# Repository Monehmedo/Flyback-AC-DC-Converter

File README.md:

Flyback AC-DC Converter — 12V SMPS
PCB Design Project | KiCad 10.0.1 | Mohamed Elashmawi
A complete Switch-Mode Power Supply (SMPS) designed from scratch using the Flyback
topology, converting 230VAC mains input to a regulated 12V DC output. This project
covers full schematic design, PCB layout, and 3D validation.

⚡Specifications

Parameter Value

Input Voltage 230VAC (50Hz)
Output Voltage 12V DC

Topology Flyback (Isolated SMPS)

PWM Controller VIPer22A (DIP-8)

Transformer EE25-13-7

Rectifier Bridge KBP206

Output Diode SB360 (Schottky)

Feedback / Isolation EL817 Optocoupler + TL431

Input Protection Varistor + NTC Thermistor + Fuse (500mA)

EMI Filter Schaffner RN102-0.3-02-12M

🔧Circuit Architecture

The design is divided into four functional blocks:

1.🔌Input Filter ( Eingangsfilter )

Varistor (RV1): Overvoltage/surge protection

NTC Thermistor (TH1): Inrush current limiting at startup

EMI Filter (FL1 - Schaffner RN102): Common-mode noise suppression

Fuse (F1 - 500mA): Short-circuit protection

X-Capacitor (C1 - 100nF/275VAC): Differential-mode noise filtering

2.⚙️Power Stage ( Leistungsstufe )

Bridge Rectifier (D15 - KBP206): Full-wave AC-to-DC conversion

Bulk Capacitor (C2 - 22µF/400V): DC bus smoothing

VIPer22A PWM Controller (U1): Integrated MOSFET + PWM control IC

Fast Recovery Diode (D1 - FR107): Demagnetization protection

Flyback Transformer (T1 - EE25-13-7): Galvanic isolation & energy transfer

RCD Snubber (R3, C3, D1): MOSFET drain spike clamping

3.🔋DC Output ( DC Ausgang )

Schottky Diode (D5 - SB360): Low forward-drop rectification

Output Inductance (L1 - 10µH): Output ripple reduction

Output Capacitors (C5–C8 - 470µF/16V): Output voltage smoothing

Status LED (D3) + Resistors: Power-on indication

4.🔁Feedback / Regulation ( Rückkopplung )

TL431 (U2): Programmable precision shunt regulator

EL817 Optocoupler (U3): Galvanic isolation of feedback signal

Trimmer (RV3 - 500Ω): Output voltage fine adjustment

Divider Network (R6, R7, R4, R5): Voltage sensing

📐Key Design Decisions

RCD Snubber Design

The Flyback topology generates high-voltage spikes on the MOSFET drain during turn-off

due to transformer leakage inductance. An RCD clamp circuit (R3 = 100kΩ, C3 =

2.2nF/1kV, D1 = FR107) was implemented to absorb these spikes and protect the VIPer22A

internal MOSFET.

Optocoupler Feedback Loop

The EL817 optocoupler in combination with the TL431 shunt regulator creates a stable,

isolated feedback loop. This ensures regulated 12V output regardless of input voltage or

load variations.

EMI & Input Filtering

A Schaffner common-mode choke (FL1) combined with an X-capacitor (C1) and NTC

thermistor (TH1) provides a complete input EMI filter, preventing conducted noise from

entering the mains supply.

📦Bill of Materials (Key Components)

Reference Component Value / Part Number

U1 PWM Controller VIPer22ADIP-E

U2 Shunt Regulator TL431DBZ

U3 Optocoupler EL817

T1 Transformer EE25-13-7

D5 Schottky Diode SB360

D15 Bridge Rectifier KBP206

D1 Fast Recovery Diode FR107

FL1 EMI Filter Schaffner RN102-0.3-02-12M

RV1 Varistor 275VAC

TH1 NTC Thermistor —

C2 Bulk Capacitor 22µF / 400V

C5–C8 Output Capacitors 470µF / 16V

RV3 Trimmer 500Ω

🎓What I Learned

Complete SMPS design flow from topology selection to PCB manufacturing files

Deep understanding of the VIPer22A integrated PWM controller and its peripheral

design

RCD snubber calculation for MOSFET protection in flyback converters

Optocoupler feedback loop design for isolated DC-DC regulation

PCB layout best practices for mixed high-voltage / low-voltage circuits

Proper grounding strategies to minimize EMI in switch-mode supplies

Integration of STEP 3D models in KiCad for component validation

⚠️Safety Notice

This project involves dangerous mains voltages (230VAC). The schematic and PCB are

provided for educational and design reference only. Do not build or test this circuit

without proper knowledge, equipment, and safety precautions.

👤Author

Mohamed Elashmawi B.Sc. Elektrotechnik und Informationstechnik — TU Dortmund

📄License
This project is open-source for educational purposes. Feel free to use, adapt, and learn from
it — credits appreciated!

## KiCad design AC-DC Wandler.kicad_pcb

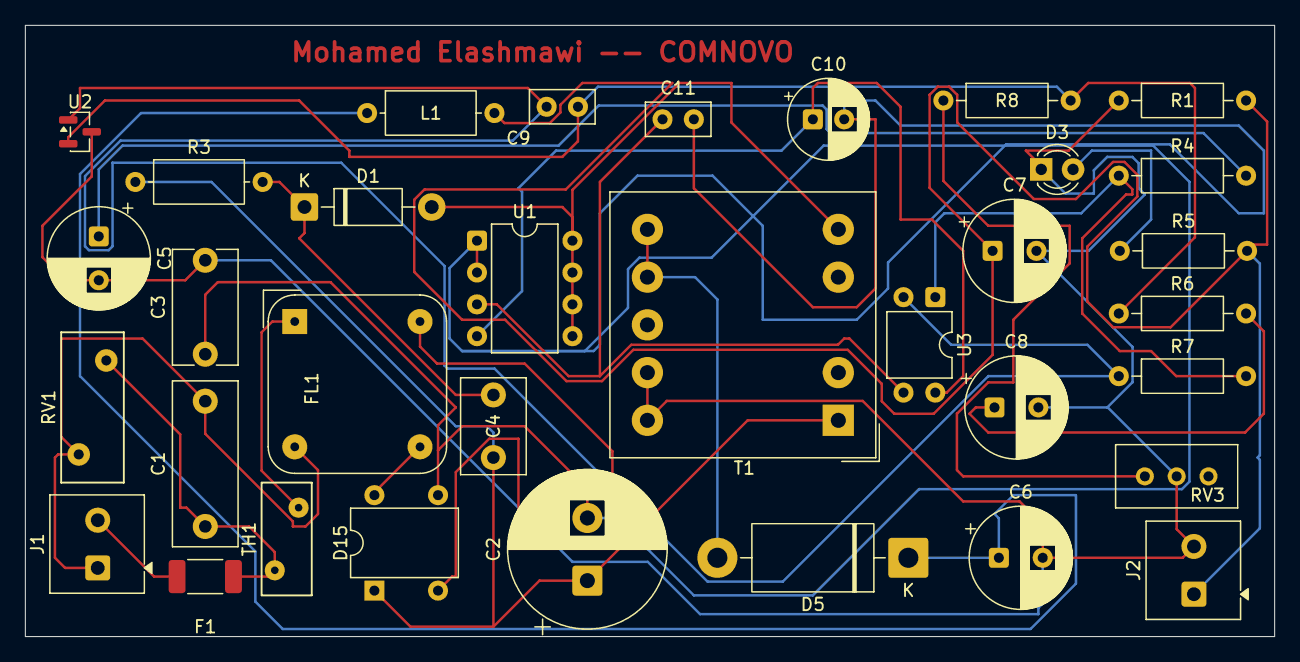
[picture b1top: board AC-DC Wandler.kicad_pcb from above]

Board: 2 copper layers, 99.7 x 48.8 mm, 34 parts (0 on the bottom side), 23 nets.

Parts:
C1: 100nF-275VAC; C_Rect_L13.0mm_W5.0mm_P10.00mm_FKS3_FKP3_MKS4
C2: 22uF-400V; CP_Radial_D12.5mm_P5.00mm
C3: 2.2nF-1KV; C_Disc_D9.0mm_W5.0mm_P7.50mm
C4: 10nF-1KV; C_Disc_D7.5mm_W5.0mm_P5.00mm
C5, C6, C7, C8: 470μF-16V; CP_Radial_D8.0mm_P3.50mm
C9: 100nF; C_Disc_D5.0mm_W2.5mm_P2.50mm
C10: 100uF-16V; CP_Radial_D6.3mm_P2.50mm
C11: 10nF-50v; C_Disc_D5.0mm_W2.5mm_P2.50mm
D1: FR107; D_DO-41_SOD81_P10.16mm_Horizontal
D3: 3mm-LED; LED_D3.0mm
D5: SB360; D_DO-201AD_P15.24mm_Horizontal
D15: KBP206; Diode_Bridge_DIP-4_W7.62mm_P5.08mm
F1: 500mA; Fuse_2010_5025Metric
FL1: Choke_Schaffner_RN102-0.3-02-12M; Choke_Schaffner_RN102-04-14.0x14.0mm
J1: AC Eingang; TerminalBlock_Phoenix_MKDS-1-2-3.81_1x02_P3.81mm_Horizontal
J2: DC Ausgang; TerminalBlock_Phoenix_MKDS-1-2-3.81_1x02_P3.81mm_Horizontal
L1: 10µH; L_Axial_L7.0mm_D3.3mm_P10.16mm_Horizontal_Fastron_MICC
R1: 330; R_Axial_DIN0207_L6.3mm_D2.5mm_P10.16mm_Horizontal
R3: 100K-1W; L_Axial_L7.0mm_D3.3mm_P10.16mm_Horizontal_Fastron_MICC
R4: 2.2K; R_Axial_DIN0207_L6.3mm_D2.5mm_P10.16mm_Horizontal
R5: 1K; R_Axial_DIN0207_L6.3mm_D2.5mm_P10.16mm_Horizontal
R6: 18K; R_Axial_DIN0207_L6.3mm_D2.5mm_P10.16mm_Horizontal
R7: 4.7K; R_Axial_DIN0207_L6.3mm_D2.5mm_P10.16mm_Horizontal
R8: 3.9K; R_Axial_DIN0207_L6.3mm_D2.5mm_P10.16mm_Horizontal
RV1: Varistor; RV_Disc_D12mm_W5mm_P7.5mm
RV3: 500R_Trim; Potentiometer_Bourns_3296W_Vertical
T1: EE25-13-7; Transformer_Myrra_EF20_7408x
TH1: Thermistor_NTC; RV_Disc_D9mm_W4mm_P5mm
U1: VIPer22ADIP-E; DIP-8_W7.62mm
U2: TL431DBZ; SOT-23
U3: EL817; DIP-4_W7.62mm

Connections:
+12V_1: C5.1, R4.2
+12V_2: C8.1, R6.2
/DC Line: C2.1, C4.1, D15.1 (+), R3.1, T1.1 (AA)
GND1: C2.2, C3.1, C10.2, C11.2, D15.3 (-), U1.1 (S), U1.2 (S)
GND2: C3.2, C5.2, C6.2, C7.2, C8.2, D3.1 (K), J2.2, R1.1, RV3.2, T1.9 (SB), T1.10 (SA), U2.3 (A)
unnamed: C1.1, F1.2, RV1.1, TH1.2
unnamed: D1.2 (A), T1.5 (AB), U1.5 (D), U1.6 (D), U1.7 (D), U1.8 (D)
unnamed: C4.2, D1.1 (K), R3.2
unnamed: D3.2 (A), R5.1
unnamed: D5.2 (A), T1.6 (SC), T1.7 (SD)
unnamed: C6.1, D5.1 (K), L1.1
unnamed: D15.2, FL1.2
unnamed: D15.4, FL1.4
unnamed: FL1.1, TH1.1
unnamed: C1.2, FL1.3, J1.1, RV1.2
unnamed: F1.1, J1.2
unnamed: C7.1, J2.1, L1.2, R1.2, R5.2
unnamed: R4.1, R7.2, U3.1
unnamed: R8.1, RV3.1
unnamed: C11.1, U1.3 (FB), U3.3
unnamed: C10.1, U1.4 (VDD), U3.4
unnamed: C9.1, R7.1, U2.1 (K), U3.2
unnamed: C9.2, R6.1, R8.2, U2.2 (REF)

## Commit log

2026-06-26 Add KiCad project files and project images
